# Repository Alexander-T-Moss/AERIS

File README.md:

#  AERIS – Air Quality Monitoring System 

**AERIS** is an open-source air quality monitor built around an **ESP32** microcontroller, **SEN55** module and custom breakout board. It measures and reports environmental parameters, such as particulate matter, VOCs, humidity and temperature in real-time to either a Home Assistant instance (through ESPHome) or a local web app.

<br/>

## Project Goals
- **Accurate & Trustable Data** – Obtained by using the factory-calibrated SEN55 and thermally isolating the unit from the other electronics.
- **Low-Cost** – AERIS' DIY-friendly design approach and BOM considerations result in a unit cost that is more than halved when compared to equivalent off-the-shelf products, at only £35/€40/$48.
- **Full Hardware Utilisation** –  Using any of the provided firmware options, every last bit of information is extracted from AERIS, getting the most "bang-for-buck" out of the used hardware.
- **Simple Assembly** – From a snap-fit case to a breakout PCB, assembly is streamlined to require minimal tools and only a few minutes.
- **Accessible Project** - Care is taken to decrease friction from obtaining hardware to building an AERIS device. Unlike other monitors, AERIS can be used fully as a standalone unit without needing a Home Assistant instance. 

<br/>

## Feature List
<details>
<summary><b>Comprehensive Sensor Array</b></summary>
<br/>

- Temperature
- Relative Humidity
- Absolute Humidity (Approximation)
- VOC Index
- Particulate Matter
  - PM1.0
  - PM2.5
  - PM4.0
  - PM10.0
- Nitrogen Oxide Index (NOx)
- Carbon Dioxide (w/ Add-On Board)
- Atmospheric Pressure (w/ Add-On Board)

</details>

<details>
<summary><b>ESPHome Integration</b></summary>
<br/>  
Requires a Home Assistant instance; alternatively, AERIS can be operated without Home Assistant through its standalone mode.
<br/>
<br/>
</details>

<details>
<summary><b>Standalone Mode</b></summary>
<br/>
The ESP controller can host a local webpage, circumventing the need for a Home Assistant instance.
<br/> 
<br/>
</details>

<details>
<summary><b>1.54" OLED Display</b></summary>
<br/>
Configurable to either show key data at a glance or show in-depth information reported by AERIS.
<br/> 
<br/>
</details>

<details>
<summary><b>Snap-Fit Case</b></summary>
<br/>
For an easy assembly, reduced BOM and clean finish, the case is designed to snap-fit together.
<br/>
<br/>
</details>

<br/>

## More Information
Interested in this project or building an AERIS unit? Visit the [official documentation](https://aeris-docs.xyz) site for more info.

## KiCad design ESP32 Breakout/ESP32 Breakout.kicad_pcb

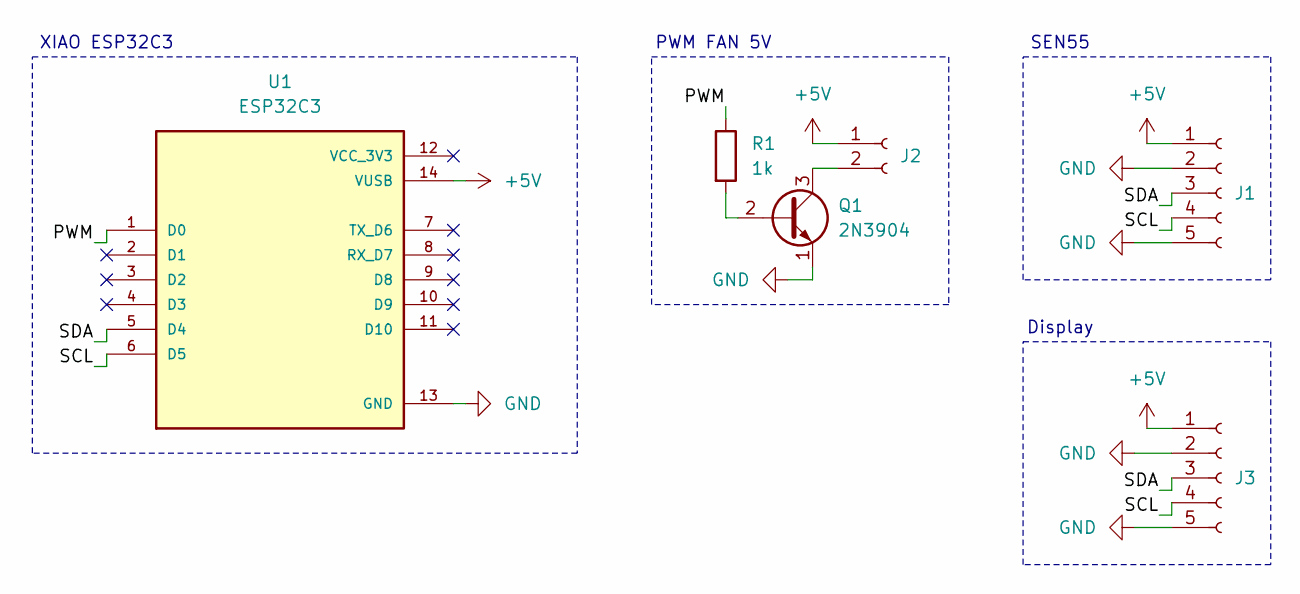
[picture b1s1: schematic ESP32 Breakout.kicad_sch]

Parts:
J1, J3: Conn_01x05_Socket; JST_XH_B5B-XH-A_1x05_P2.50mm_Vertical
J2: Conn_01x02_Socket; JST_XH_B2B-XH-A_1x02_P2.50mm_Vertical
Q1: 2N3904; TO-92_Inline
R1: 1k; R_Axial_DIN0207_L6.3mm_D2.5mm_P7.62mm_Horizontal
U1: ESP32C3; XIAO_ESP32; PARTREV 23/05/2022

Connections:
+5V: J1.1, J2.1, J3.1, U1.14 (VUSB)
/PWM: R1.1, U1.1 (D0)
/SCL: J1.4, J3.4, U1.6 (D5)
/SDA: J1.3, J3.3, U1.5 (D4)
GND: J1.2, J1.5, J3.2, J3.5, Q1.1 (E), U1.13 (GND)
unnamed: J2.2, Q1.3 (C)
unnamed: Q1.2 (B), R1.2

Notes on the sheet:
SEN55
PWM FAN 5V
Display
XIAO ESP32C3

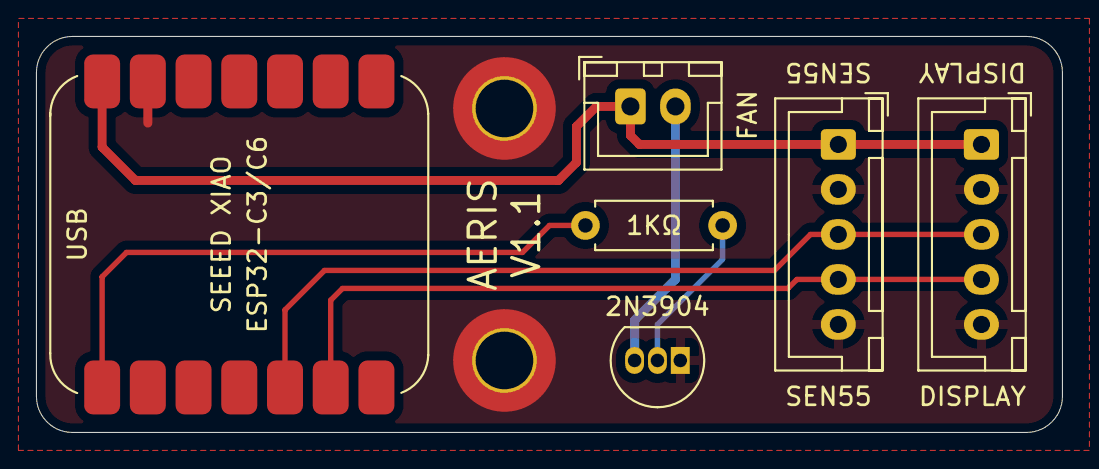
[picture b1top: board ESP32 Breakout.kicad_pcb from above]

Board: 2 copper layers, 57.0 x 22.0 mm, 6 parts (0 on the bottom side), 7 nets.

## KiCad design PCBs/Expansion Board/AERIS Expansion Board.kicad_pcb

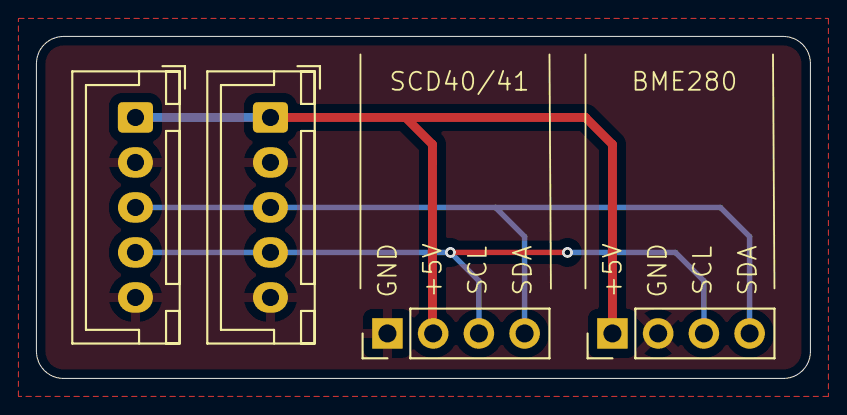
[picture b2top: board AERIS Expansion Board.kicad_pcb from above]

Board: 2 copper layers, 43.0 x 19.0 mm, 4 parts (0 on the bottom side), 4 nets.

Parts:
J1, J2: Conn_01x05_Socket; JST_XH_B5B-XH-A_1x05_P2.50mm_Vertical
J3, J4: Conn_01x04_Pin; PinHeader_1x04_P2.54mm_Vertical

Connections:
/+5V: J1.1, J2.1, J3.1, J4.2
/GND: J1.2, J1.5, J2.2, J2.5, J3.2, J4.1
/SCL: J1.4, J2.4, J3.3, J4.3
/SDA: J1.3, J2.3, J3.4, J4.4

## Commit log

2025-07-31 Added Source CAD
2025-08-12 Upload V1.0
2025-08-13 File Update
2025-08-13 Added Images
2025-08-13 Rename images
2025-08-25 Rename
2025-08-25 File Restructure
2025-08-25 Restructure
2025-08-25 Uploaded CAD
2025-08-25 Upload STLs
2025-08-25 Remove duplicates
2025-09-02 Added PCB CAD
2025-09-02 Added Solder Jigs
2025-09-04 Update PCBs
    Swap to just ESP32C6
    Make footprint libraries project and not global
2025-09-06 Production Check

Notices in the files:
README.md:
License: GPL-3.0
